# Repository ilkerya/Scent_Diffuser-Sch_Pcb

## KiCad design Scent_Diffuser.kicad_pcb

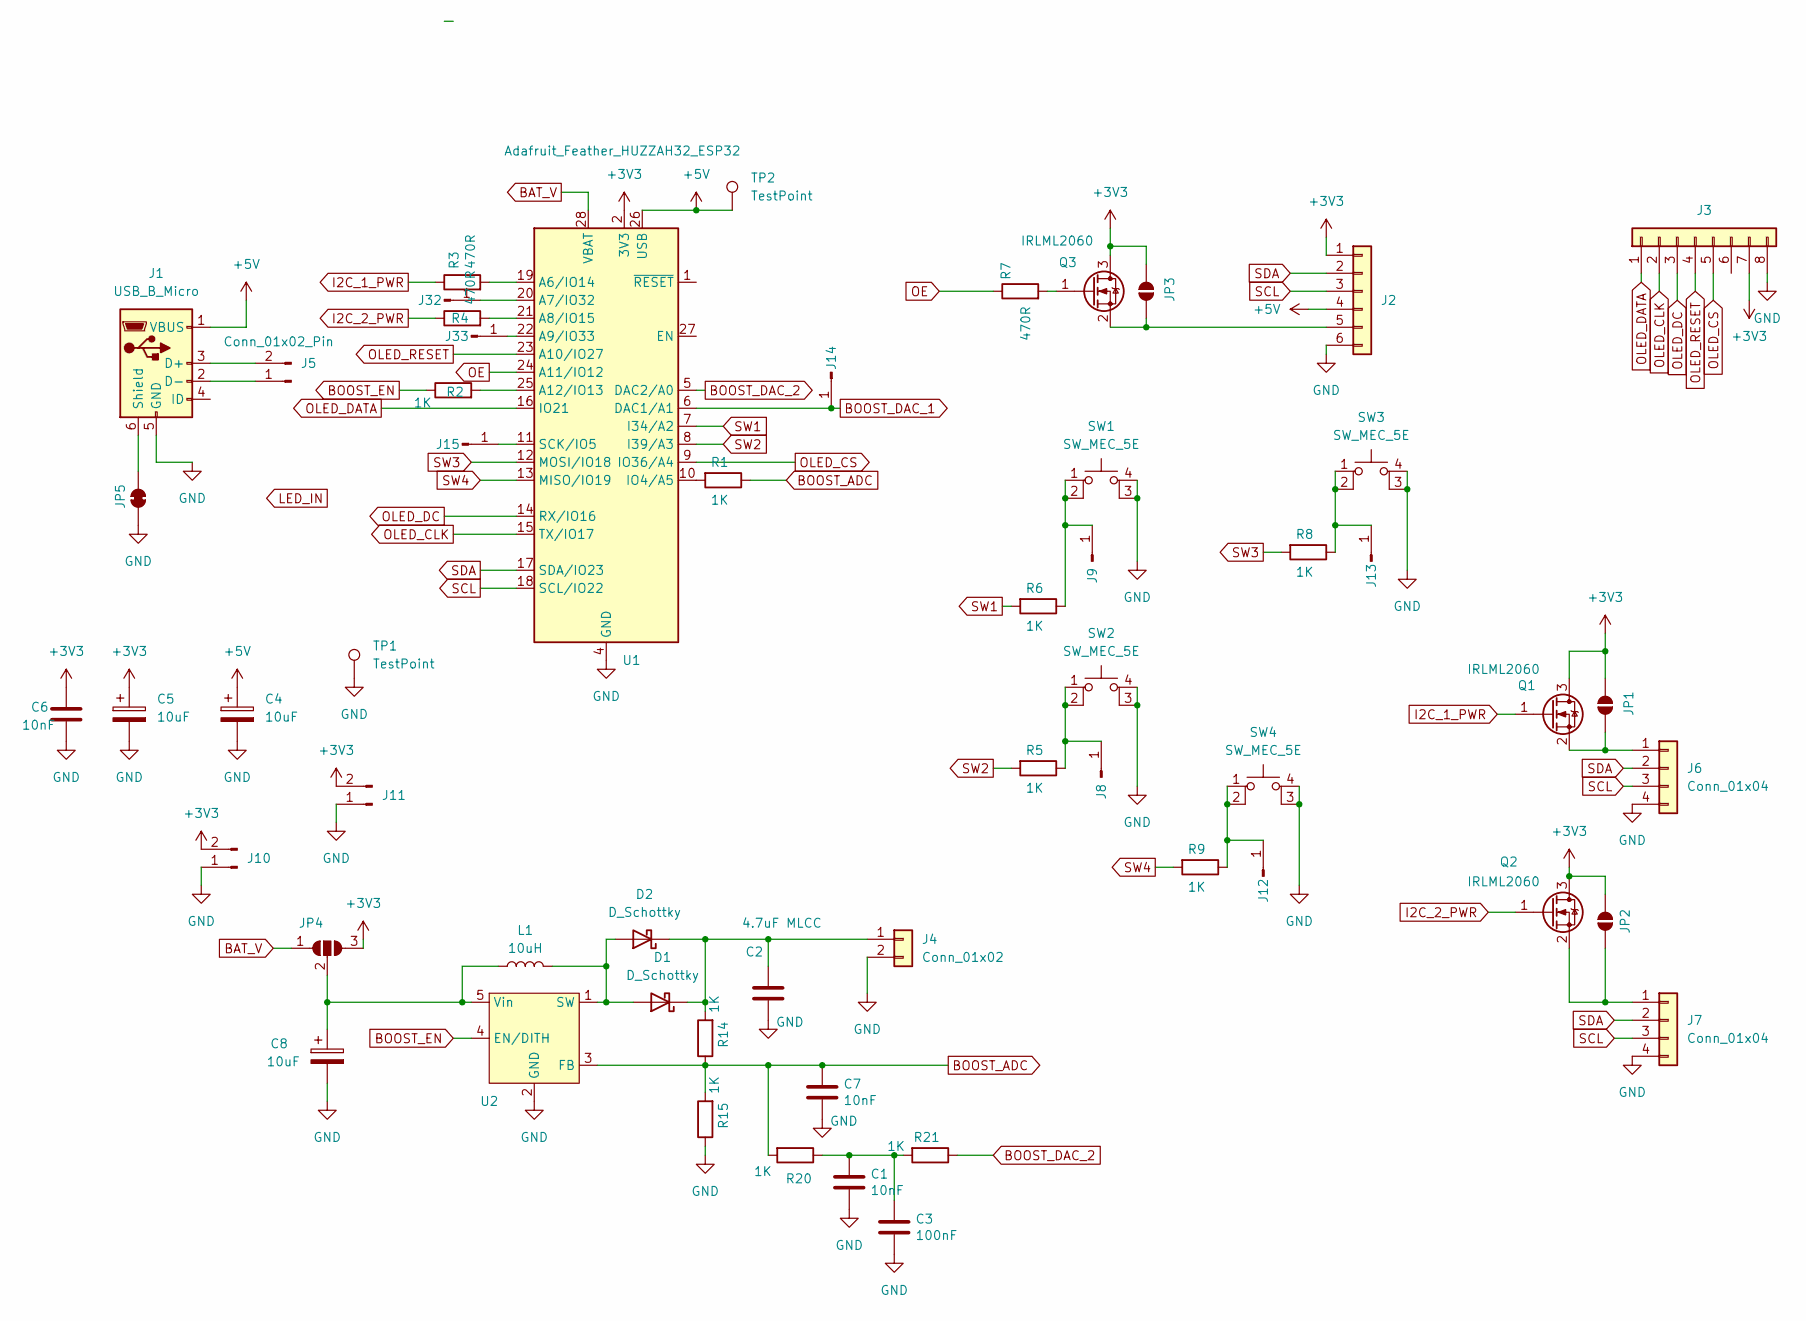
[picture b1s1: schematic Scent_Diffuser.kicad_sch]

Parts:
C1: 10nF; C_0805_2012Metric_Pad1.18x1.45mm_HandSolder
C2: 4.7uF MLCC; C_1206_3216Metric_Pad1.33x1.80mm_HandSolder
C3: 100nF; C_1206_3216Metric_Pad1.33x1.80mm_HandSolder
C4: 10uF; C_1206_3216Metric
C5, C8: 10uF; C_Elec_5x5.8
C6, C7: 10nF; C_1206_3216Metric_Pad1.33x1.80mm_HandSolder
D1: D_Schottky; D_SOD-523
D2: D_Schottky; D_SMF
J1: USB_B_Micro; USB_Micro-B_Molex-105017-0001
J2: Conn_01x06; PinSocket_1x06_P2.54mm_Vertical
J3: Conn_01x08; PinSocket_1x08_P2.54mm_Vertical
J4: Conn_01x02; PinSocket_1x02_P2.54mm_Vertical
J5, J10, J11: Conn_01x02_Pin; PinHeader_1x02_P2.54mm_Vertical
J6, J7: Conn_01x04; PinSocket_1x04_P2.54mm_Vertical
J8, J9, J12, J13, J14, J15, J32, J33: Conn_01x01_Pin; TestPoint_THTPad_2.0x2.0mm_Drill1.0mm
JP1, JP2, JP3: SolderJumper_2_Open; SolderJumper-2_P1.3mm_Open_RoundedPad1.0x1.5mm
JP4: SolderJumper_3_Open; SolderJumper-3_P1.3mm_Open_RoundedPad1.0x1.5mm
JP5: SolderJumper_2_Bridged; SolderJumper-2_P1.3mm_Bridged2Bar_RoundedPad1.0x1.5mm
L1: 10uH; L_1206_3216Metric_Pad1.22x1.90mm_HandSolder
Q1, Q2, Q3: IRLML2060; SOT-23
R1, R2, R5, R6, R8, R9, R14, R15, R20, R21: 1K; R_0805_2012Metric
R3, R4, R7: 470R; R_0805_2012Metric_Pad1.20x1.40mm_HandSolder
SW1, SW2, SW3, SW4: SW_MEC_5E; SW_PUSH_6mm_4_pin
TP1, TP2: TestPoint; TestPoint_THTPad_2.0x2.0mm_Drill1.0mm
U1: Adafruit_Feather_HUZZAH32_ESP32; Adafruit_Feather
U2: TSOT-23-5_HandSoldering

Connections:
+3V3: C5.1, C6.1, J2.1, J3.7, J10.2, J11.2, JP1.2 (B), JP2.2 (B), JP3.2 (B), JP4.3 (B), Q1.3 (D), Q2.3 (D), Q3.3 (D), U1.2 (3V3)
+5V: C4.1, J1.1 (VBUS), J2.4, TP2.1, U1.26 (USB)
BAT_V: JP4.1 (A), U1.28 (VBAT)
BOOST_ADC: C7.1, R1.1, R14.1, R15.2, R20.2, U2.3 (FB)
BOOST_DAC_1: J14.1, U1.6 (DAC1/A1)
BOOST_DAC_2: R21.1, U1.5 (DAC2/A0)
BOOST_EN: R2.1, U2.4 (EN/DITH)
GND: C1.2, C2.2, C3.2, C4.2, C5.2, C6.2, C7.2, C8.2, J1.5 (GND), J2.6, J3.8, J4.2, J6.4, J7.4, J10.1, J11.1, JP5.1 (A), R15.1, SW1.3 (K), SW1.4 (A), SW2.3 (K), SW2.4 (A), SW3.3 (K), SW3.4 (A), SW4.3 (K), SW4.4 (A), TP1.1, U1.4 (GND), U2.2 (GND)
I2C_1_PWR: Q1.1 (G), R3.1
I2C_2_PWR: Q2.1 (G), R4.1
unnamed: C1.1, C3.1, R20.1, R21.2
unnamed: D1.2 (A), D2.2 (A), L1.2, U2.1 (SW)
unnamed: C2.1, D1.1 (K), D2.1 (K), J4.1, R14.2
unnamed: J1.3 (D+), J5.2
unnamed: J1.2 (D-), J5.1
unnamed: J1.6 (Shield), JP5.2 (B)
unnamed: J2.5, JP3.1 (A), Q3.2 (S)
unnamed: J6.1, JP1.1 (A), Q1.2 (S)
unnamed: J7.1, JP2.1 (A), Q2.2 (S)
unnamed: J8.1, R5.1, SW2.1, SW2.2
unnamed: J9.1, R6.1, SW1.1, SW1.2
unnamed: J12.1, R9.1, SW4.1, SW4.2
unnamed: J13.1, R8.1, SW3.1, SW3.2
unnamed: J15.1, U1.11 (SCK/IO5)
unnamed: J32.1, U1.20 (A7/IO32)
unnamed: J33.1, U1.22 (A9/IO33)
unnamed: C8.1, JP4.2 (C), L1.1, U2.5 (Vin)
unnamed: Q3.1 (G), R7.2
unnamed: R3.2, U1.19 (A6/IO14)
unnamed: R4.2, U1.21 (A8/IO15)
unnamed: R2.2, U1.25 (A12/IO13)
unnamed: R1.2, U1.10 (IO4/A5)
OE: R7.1, U1.24 (A11/IO12)
OLED_CLK: J3.2, U1.15 (TX/IO17)
OLED_CS: J3.5, U1.9 (IO36/A4)
OLED_DATA: J3.1, U1.16 (IO21)
OLED_DC: J3.3, U1.14 (RX/IO16)
OLED_RESET: J3.4, U1.23 (A10/IO27)
SCL: J2.3, J6.3, J7.3, U1.18 (SCL/IO22)
SDA: J2.2, J6.2, J7.2, U1.17 (SDA/IO23)
SW1: R6.2, U1.7 (I34/A2)
SW2: R5.2, U1.8 (I39/A3)
SW3: R8.2, U1.12 (MOSI/IO18)
SW4: R9.2, U1.13 (MISO/IO19)

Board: 2 copper layers, 57 parts (0 on the bottom side), 44 nets, no tracks yet.
